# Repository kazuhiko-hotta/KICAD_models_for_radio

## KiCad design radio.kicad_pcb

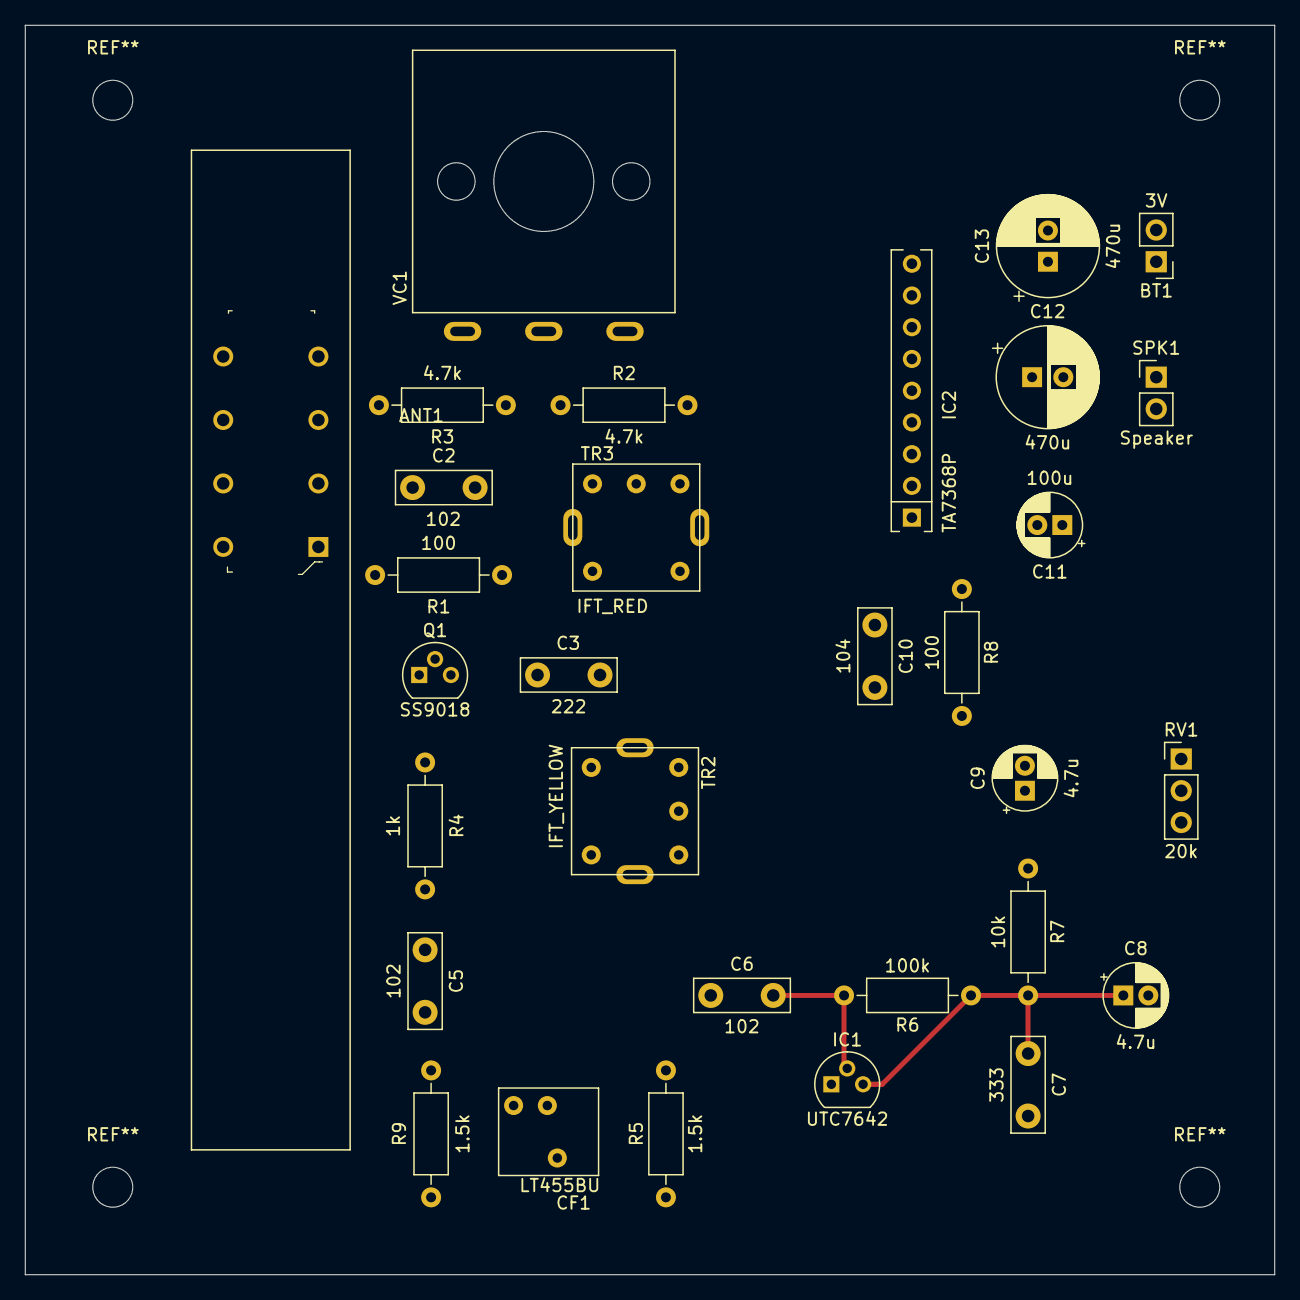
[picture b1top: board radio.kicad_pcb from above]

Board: 2 copper layers, 100.0 x 100.0 mm, 31 parts (0 on the bottom side), 23 nets.

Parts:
ANT1: AM_ANTENNA
BT1: 3V; PinHeader_1x02_P2.54mm_Vertical
C2, C5, C6: 102; C_Disc_D7.5mm_W2.5mm_P5.00mm
C3: 222; C_Disc_D7.5mm_W2.5mm_P5.00mm
C7: 333; C_Disc_D7.5mm_W2.5mm_P5.00mm
C8, C9: 4.7u; CP_Radial_D5.0mm_P2.00mm
C10: 104; C_Disc_D7.5mm_W2.5mm_P5.00mm
C11: 100u; CP_Radial_D5.0mm_P2.00mm
C12, C13: 470u; CP_Radial_D8.0mm_P2.50mm
CF1: LT455BU
IC1: UTC7642; TO-92
IC2: TA7368P
Q1: SS9018; TO-92
R1, R8: 100; R_Axial_DIN0207_L6.3mm_D2.5mm_P10.16mm_Horizontal
R2, R3: 4.7k; R_Axial_DIN0207_L6.3mm_D2.5mm_P10.16mm_Horizontal
R4: 1k; R_Axial_DIN0207_L6.3mm_D2.5mm_P10.16mm_Horizontal
R5, R9: 1.5k; R_Axial_DIN0207_L6.3mm_D2.5mm_P10.16mm_Horizontal
R6: 100k; R_Axial_DIN0207_L6.3mm_D2.5mm_P10.16mm_Horizontal
R7: 10k; R_Axial_DIN0207_L6.3mm_D2.5mm_P10.16mm_Horizontal
RV1: 20k; PinHeader_1x03_P2.54mm_Vertical
SPK1: Speaker; PinHeader_1x02_P2.54mm_Vertical
TR2: IFT_YELLOW; IFT10mm
TR3: IFT_RED; IFT10mm
VC1: VC2

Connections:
+3V0: BT1.1, C13.1, IC2.9, R2.1, R7.1, TR2.2
GND: ANT1.2, ANT1.4, BT1.2, C7.2, C10.2, C11.2, C13.2, CF1.2, IC1.1, IC2.5, IC2.6, R3.2, R4.2, R5.1, R9.2, RV1.3, SPK1.2, TR2.4, TR3.1, VC1.2
unnamed: ANT1.1, VC1.1
unnamed: ANT1.3, C2.2
unnamed: C2.1, R1.2, R2.2, R3.1
unnamed: C3.1, TR3.2
unnamed: C3.2, Q1.1, R4.1
unnamed: C5.1, TR2.6
unnamed: C5.2, CF1.1, R9.1
unnamed: C6.1, CF1.3, R5.2
unnamed: C6.2, IC1.2, R6.2
unnamed: C7.1, C8.1, IC1.3, R6.1, R7.2
unnamed: C8.2, RV1.1
unnamed: C9.1, RV1.2
unnamed: C9.2, R8.2
unnamed: C10.1, IC2.1, R8.1
unnamed: C11.1, IC2.3
unnamed: C12.1, IC2.7
unnamed: C12.2, SPK1.1
unnamed: Q1.2, R1.1
unnamed: Q1.3, TR3.6
unnamed: TR2.3, TR3.4
VC2: TR3.3, VC1.3

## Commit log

2021-02-19 add some parts
2021-02-19 add the schematic
2021-02-19 add freecad data
2021-02-19 add the project file
2021-02-19 add the symbol libraly
2021-02-19 add the pcb design
